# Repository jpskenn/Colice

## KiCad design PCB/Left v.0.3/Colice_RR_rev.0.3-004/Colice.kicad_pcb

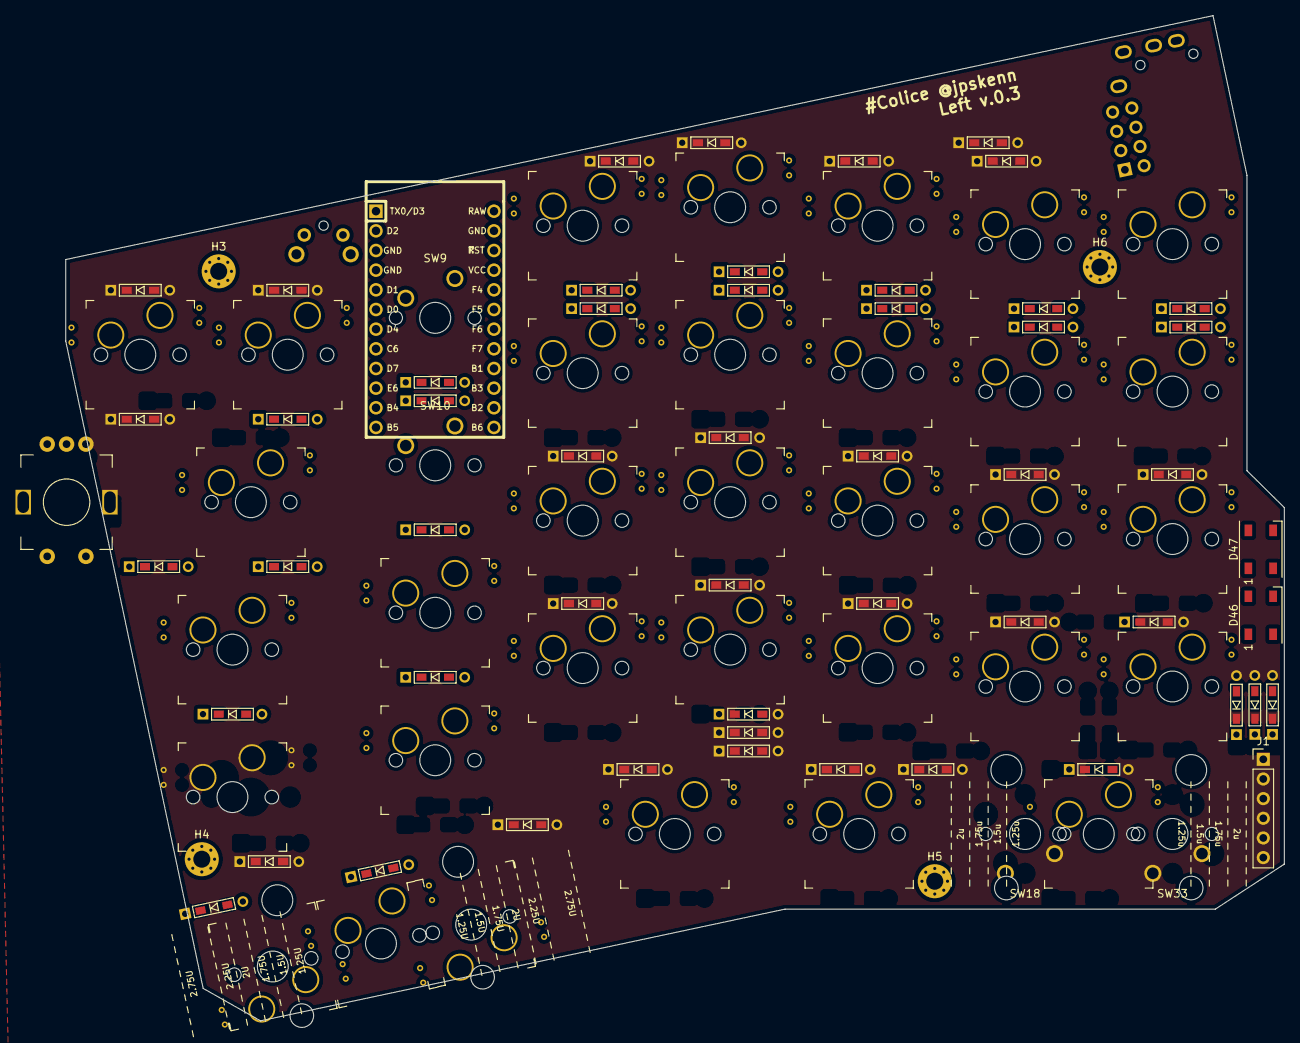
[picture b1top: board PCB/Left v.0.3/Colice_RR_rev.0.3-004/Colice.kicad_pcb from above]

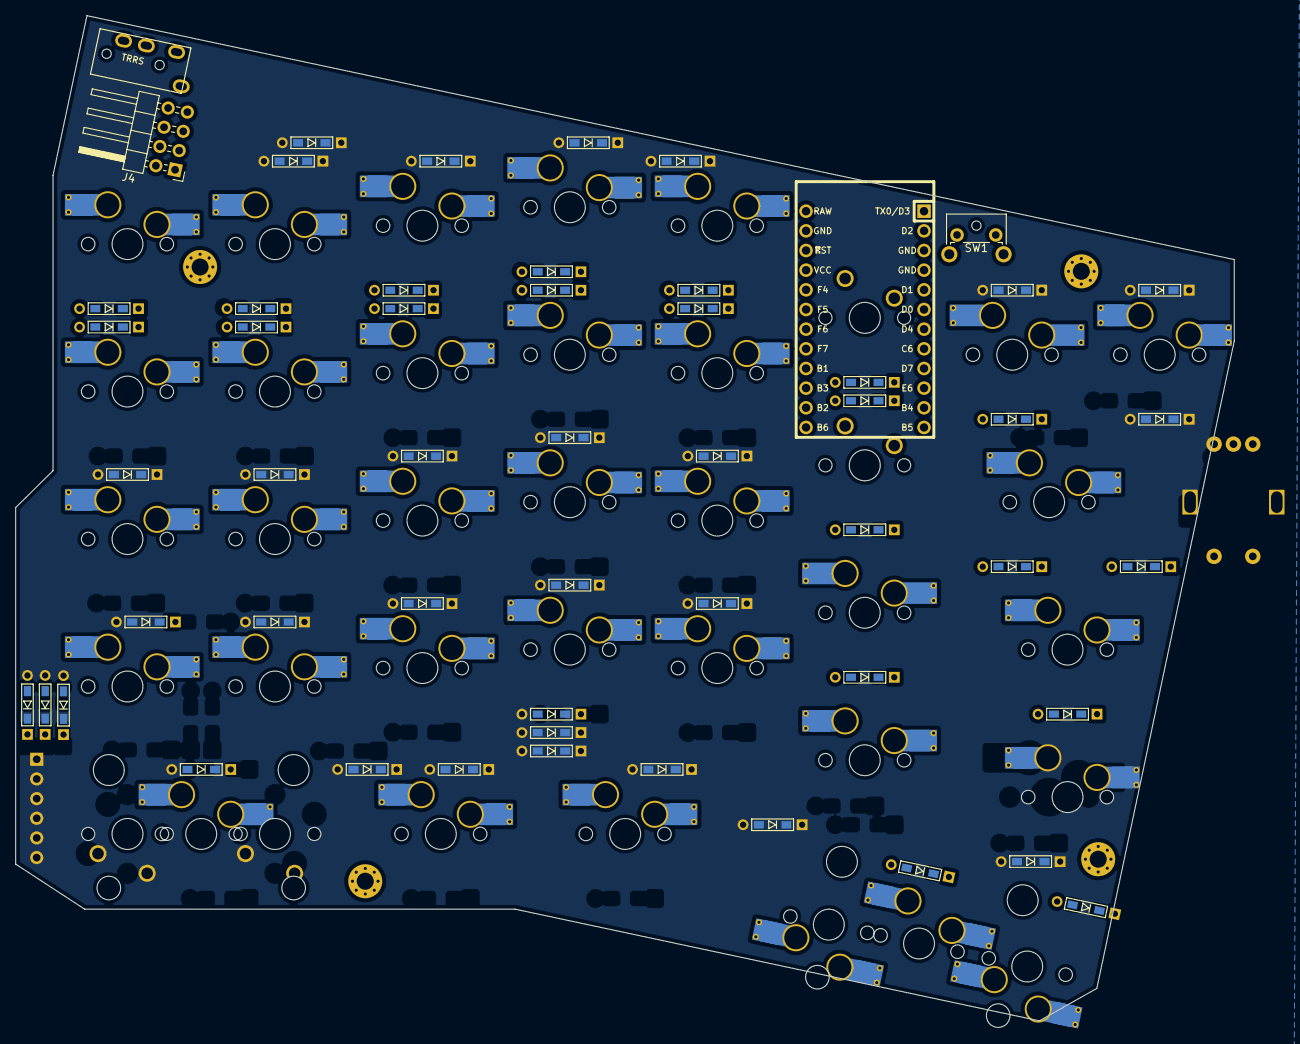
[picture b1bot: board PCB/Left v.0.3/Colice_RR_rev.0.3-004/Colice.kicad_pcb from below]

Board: 2 copper layers, 157.4 x 129.9 mm, 101 parts (4 on the bottom side), 68 nets, no tracks yet.

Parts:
D1, D2, D3, D4, D5, D6, D7, D8, D9, D10, D11, D12, D13, D14, D15, D16, D17, D18, D19, D20, D21, D22, D23, D24, D25, D26, D27, D28, D29, D30, D31, D32, D33, D34, D35, D36, D37, D38, D39, D40, D41, D42, D43, D44, D45, D48, D49, D50, D51, D52: D; D3_TH_SMD
D46, D47: WS2812B; LED_WS2812B_PLCC4_5.0x5.0mm_P3.2mm
H1: MountingHole; CherryMX_MidHeight_Choc_Hotswap_2U_Outline
H2: MountingHole; CherryMX_MidHeight_Choc_Hotswap_2.75U_Outline
H3, H4, H5, H6: MountingHole; MountingHole_2.2mm_M2_Pad_Via
J1: Conn_01x06; PinHeader_1x06_P2.54mm_Vertical
J3: MJ-4PP-9
J4: Conn_02x04_Counter_Clockwise; PinHeader_2x04_P2.54mm_Horizontal
SW1: SW_Push; SW_Tactile_SPST_Angled_MJTP1117
SW2, SW3, SW4, SW5, SW6, SW7, SW8, SW11, SW12, SW13, SW14, SW15, SW16, SW17, SW19, SW20, SW21, SW22, SW23, SW24, SW25, SW26, SW27, SW28, SW29, SW30, SW31, SW32, SW34, SW35, SW36, SW37, SW38: SW_Push; CherryMX_Hotswap_v2
SW9, SW10, SW18, SW33: SW_Push; SW_Cherry_MX1A_1.00u_PCB
SW39: Rotary_Encoder_Switch; RotaryEncoder_Alps_EC11E-Switch_Vertical_H20mm_rev2
U1: ProMicro; ArduinoProMicro

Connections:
GND1: D46.3, D47.3, J3.C, SW1.2, SW39.C, U1.3, U1.4, U1.23
unnamed: D2.2, SW2.2
unnamed: D3.2, SW3.2
unnamed: D4.1, SW4.1, SW5.1, SW6.1, SW7.1, SW8.1, SW13.1
unnamed: D5.2, SW4.2
unnamed: D6.2, SW5.2
unnamed: D7.2, SW6.2
unnamed: D8.2, SW7.2
unnamed: D9.2, SW8.2, SW13.2
unnamed: D10.1, SW9.1, SW10.1, SW11.1, SW12.1
unnamed: D11.2, SW9.2
unnamed: D12.2, SW10.2
unnamed: D13.2, SW11.2
unnamed: D14.2, SW12.2
unnamed: D16.1, SW14.1, SW15.1, SW16.1, SW17.1
unnamed: D17.2, SW14.2
unnamed: D18.2, SW15.2
unnamed: D19.2, SW16.2
unnamed: D20.2, SW17.2
unnamed: D21.2, SW18.2
unnamed: D22.1, SW19.1, SW20.1, SW21.1, SW22.1, SW23.1
unnamed: D23.2, SW19.2
unnamed: D24.2, SW20.2
unnamed: D25.2, SW21.2
unnamed: D26.2, SW22.2
unnamed: D27.2, SW23.2
unnamed: D28.1, SW24.1, SW25.1, SW26.1, SW27.1, SW28.1
unnamed: D29.2, SW24.2
unnamed: D30.2, SW25.2
unnamed: D31.2, SW26.2
unnamed: D32.2, SW27.2
unnamed: D33.2, SW28.2
unnamed: D34.1, SW29.1, SW30.1, SW31.1, SW32.1, SW33.1, SW38.1
unnamed: D35.2, SW29.2
unnamed: D36.2, SW30.2
unnamed: D37.2, SW31.2
unnamed: D38.2, SW32.2
unnamed: D39.1, J1.6
unnamed: D40.1, SW18.1, SW34.1, SW35.1, SW36.1, SW37.1
unnamed: D41.2, SW34.2
unnamed: D42.2, SW35.2
unnamed: D43.2, SW36.2
unnamed: D44.2, SW37.2
unnamed: D45.2, SW33.2, SW38.2
unnamed: D46.2, D47.4
unnamed: D48.2, J1.4
unnamed: D49.2, J1.5
unnamed: D50.2, J1.1
unnamed: D51.2, J1.2
unnamed: D52.2, J1.3
VCC: D46.1, D47.1, J3.D, U1.21
data: J3.B, U1.2
encA: SW39.A, U1.20
encB: SW39.B, U1.19
encS1: D1.1, SW2.1, SW3.1, SW39.S1
encS2: D15.2, SW39.S2
led: D46.4, U1.1
pin1: D2.1, D5.1, D11.1, D16.2, D50.1, U1.17
pin2: D6.1, D12.1, D15.1, D22.2, D51.1, U1.16
pin3: D7.1, D13.1, D28.2, D52.1, U1.15
pin4: D8.1, D14.1, D34.2, D48.1, U1.14
pin5: D3.1, D9.1, D40.2, D49.1, U1.13
pin6: D17.1, D23.1, D29.1, D35.1, D39.2, D41.1, J4.1, U1.8
pin7: D18.1, D24.1, D30.1, D36.1, D42.1, J4.2, U1.9
pin8: D1.2, D19.1, D25.1, D31.1, D37.1, D43.1, J4.3, U1.10
pin9: D4.2, D20.1, D26.1, D32.1, D38.1, D44.1, J4.4, U1.11
pin10: D10.2, D21.1, D27.1, D33.1, D45.1, J4.5, U1.12
reset: SW1.1, U1.22

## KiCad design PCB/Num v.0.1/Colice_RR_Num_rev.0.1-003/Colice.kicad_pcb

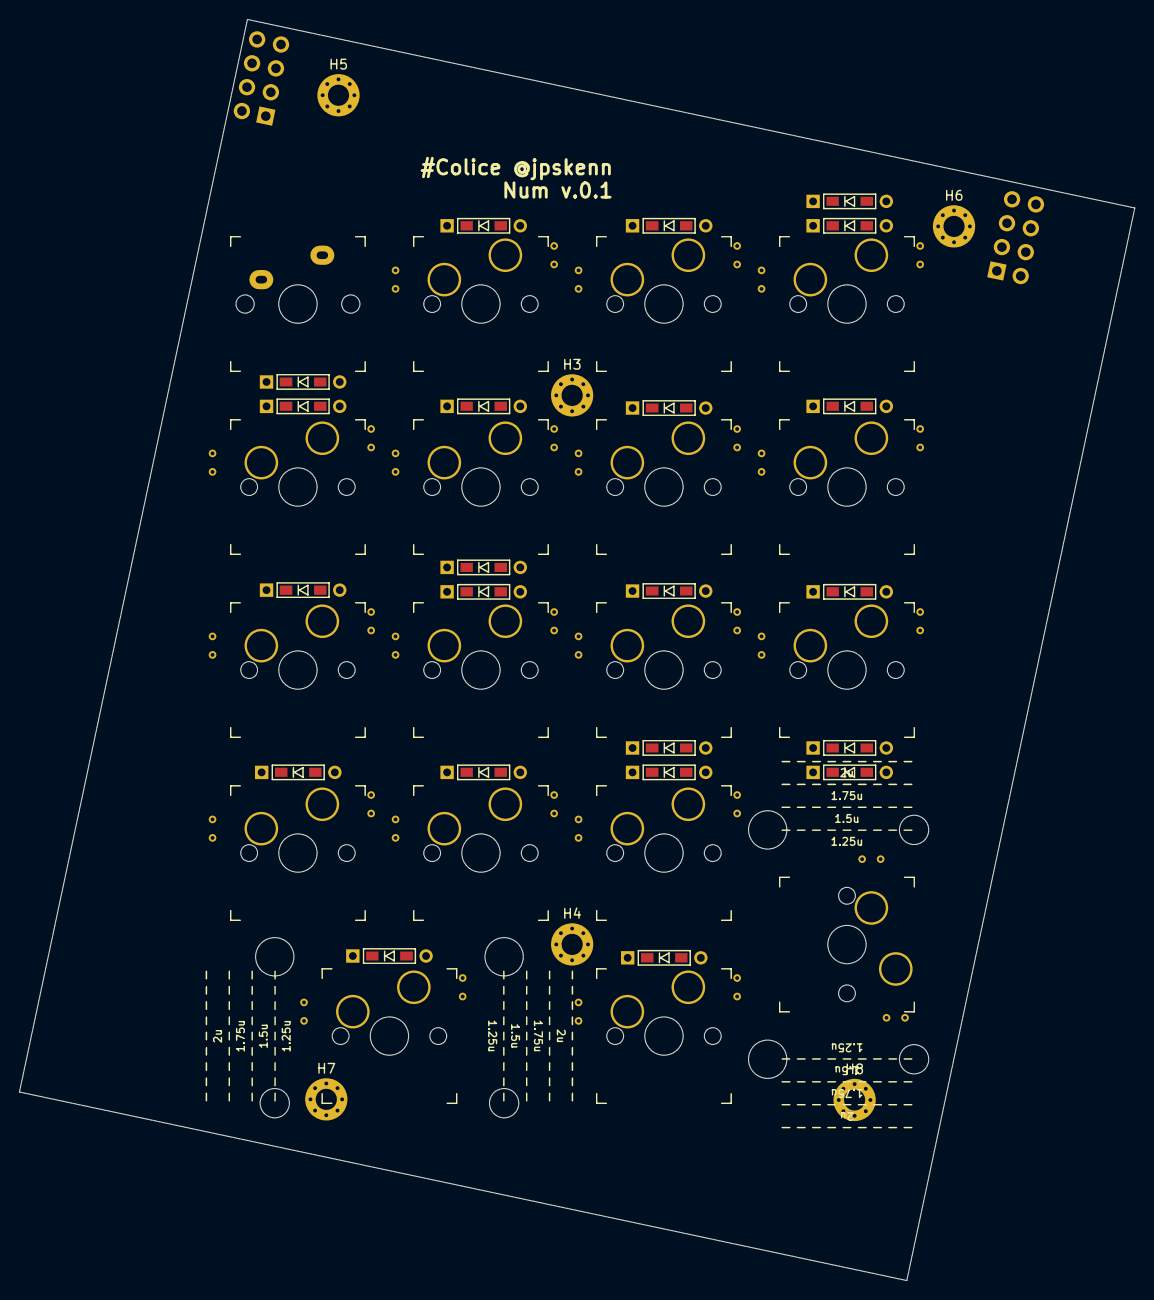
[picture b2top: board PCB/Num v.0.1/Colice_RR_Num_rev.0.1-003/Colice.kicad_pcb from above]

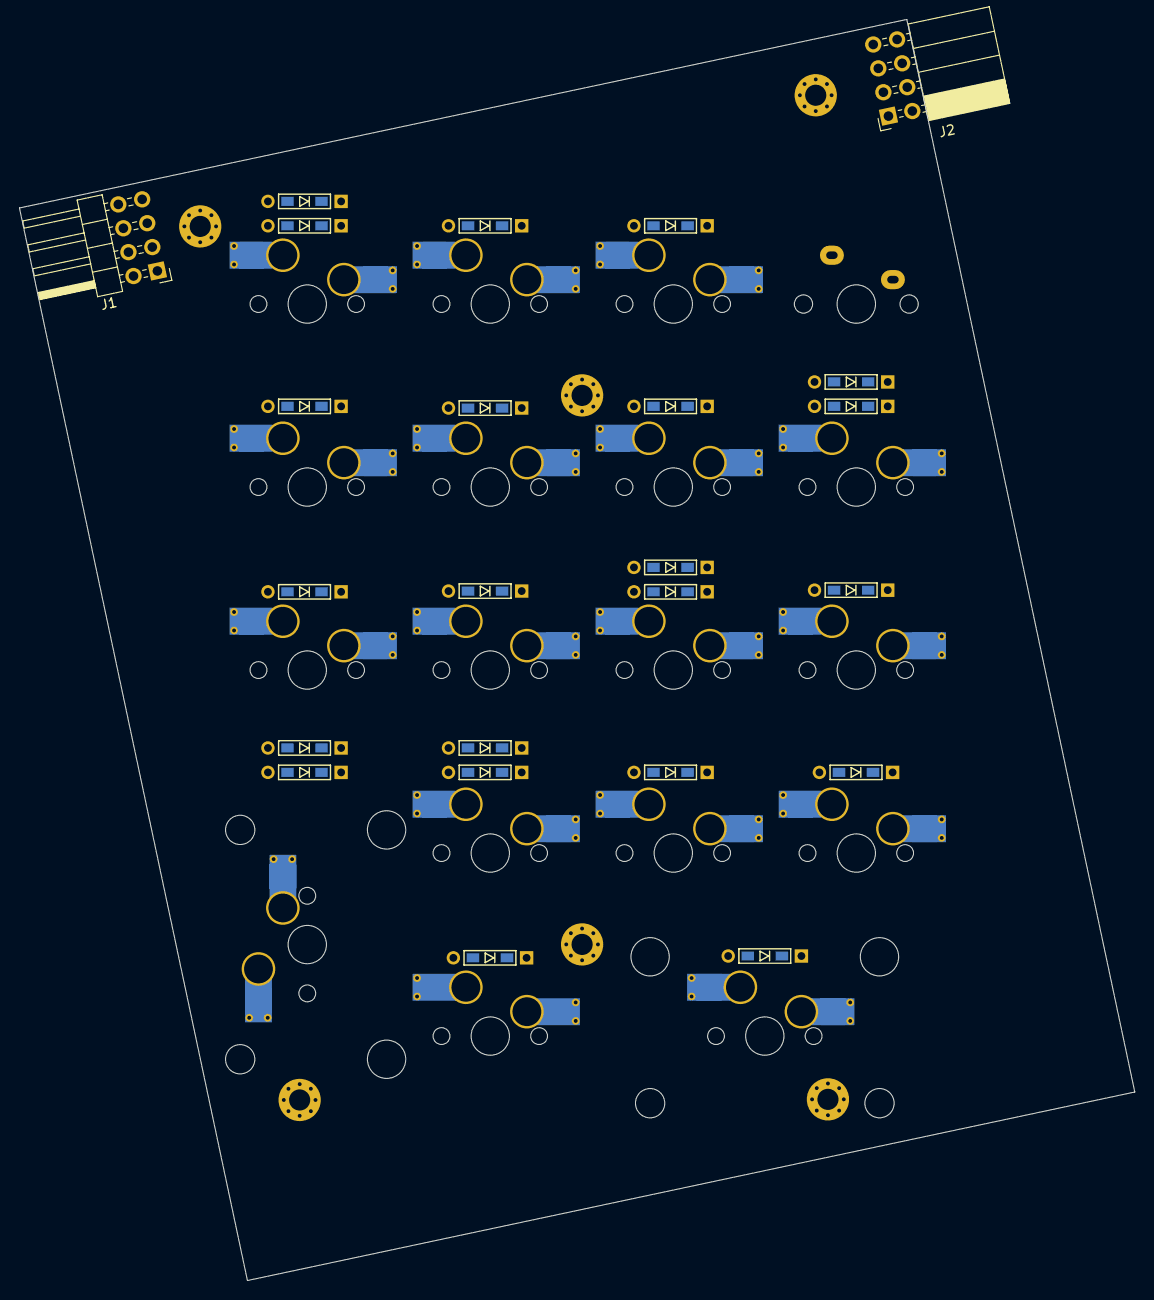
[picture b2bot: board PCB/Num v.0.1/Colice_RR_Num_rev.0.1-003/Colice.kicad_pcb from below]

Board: 2 copper layers, 116.1 x 131.3 mm, 50 parts (2 on the bottom side), 30 nets, no tracks yet.

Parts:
D1, D2, D3, D4, D5, D6, D7, D8, D9, D10, D11, D12, D13, D14, D15, D16, D17, D18, D19, D20, D21, D22: D; D3_TH_SMD
H1, H2: MountingHole; CherryMX_MidHeight_Choc_Hotswap_2U_Outline
H3, H4, H5, H6, H7, H8: MountingHole; MountingHole_2.2mm_M2_Pad_Via
J1: Conn_02x04_Counter_Clockwise; PinHeader_2x04_P2.54mm_Horizontal
J2: Conn_02x04_Counter_Clockwise; PinSocket_2x04_P2.54mm_Horizontal
SW1: SW_PUSH; CherryMX_1u
SW1#2, SW2, SW3, SW4, SW5, SW6, SW7, SW8, SW9, SW10, SW11, SW12, SW13, SW14, SW15, SW16, SW17: SW_Push; CherryMX_Hotswap_v2

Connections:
GND: J1.7, J2.7
unnamed: D1.2, SW1#2.2
unnamed: D2.2, SW2.2
unnamed: D3.2, SW3.2
unnamed: D4.2, SW4.2
unnamed: D5.2, SW5.2
unnamed: D6.2, SW6.2
unnamed: D7.2, SW7.2
unnamed: D8.2, SW8.2
unnamed: D9.2, SW9.2
unnamed: D10.2, SW10.2
unnamed: D11.2, SW11.2
unnamed: D12.2, SW12.2
unnamed: D13.2, SW13.2
unnamed: D14.2, SW14.2
unnamed: D15.2, SW15.2
unnamed: D16.2, SW16.2
unnamed: D17.2, SW17.2
unnamed: D18.1, SW14.1, SW15.1, SW16.1
unnamed: D19.1, SW1#2.1, SW2.1, SW3.1, SW4.1
unnamed: D20.1, SW7.1, SW8.1
unnamed: D21.1, SW5.1, SW6.1, SW12.1, SW13.1
unnamed: D22.1, SW9.1, SW10.1, SW11.1, SW17.1
VCC: J1.8, J2.8
data: J1.6, J2.6
pin6: D5.1, D9.1, D14.1, D19.2, J2.1
pin7: D1.1, D6.1, D10.1, D15.1, D20.2, J2.2
pin8: D2.1, D7.1, D11.1, D16.1, D21.2, J2.3
pin9: D3.1, D8.1, D12.1, D22.2, J2.4
pin10: D4.1, D13.1, D17.1, D18.2, J2.5

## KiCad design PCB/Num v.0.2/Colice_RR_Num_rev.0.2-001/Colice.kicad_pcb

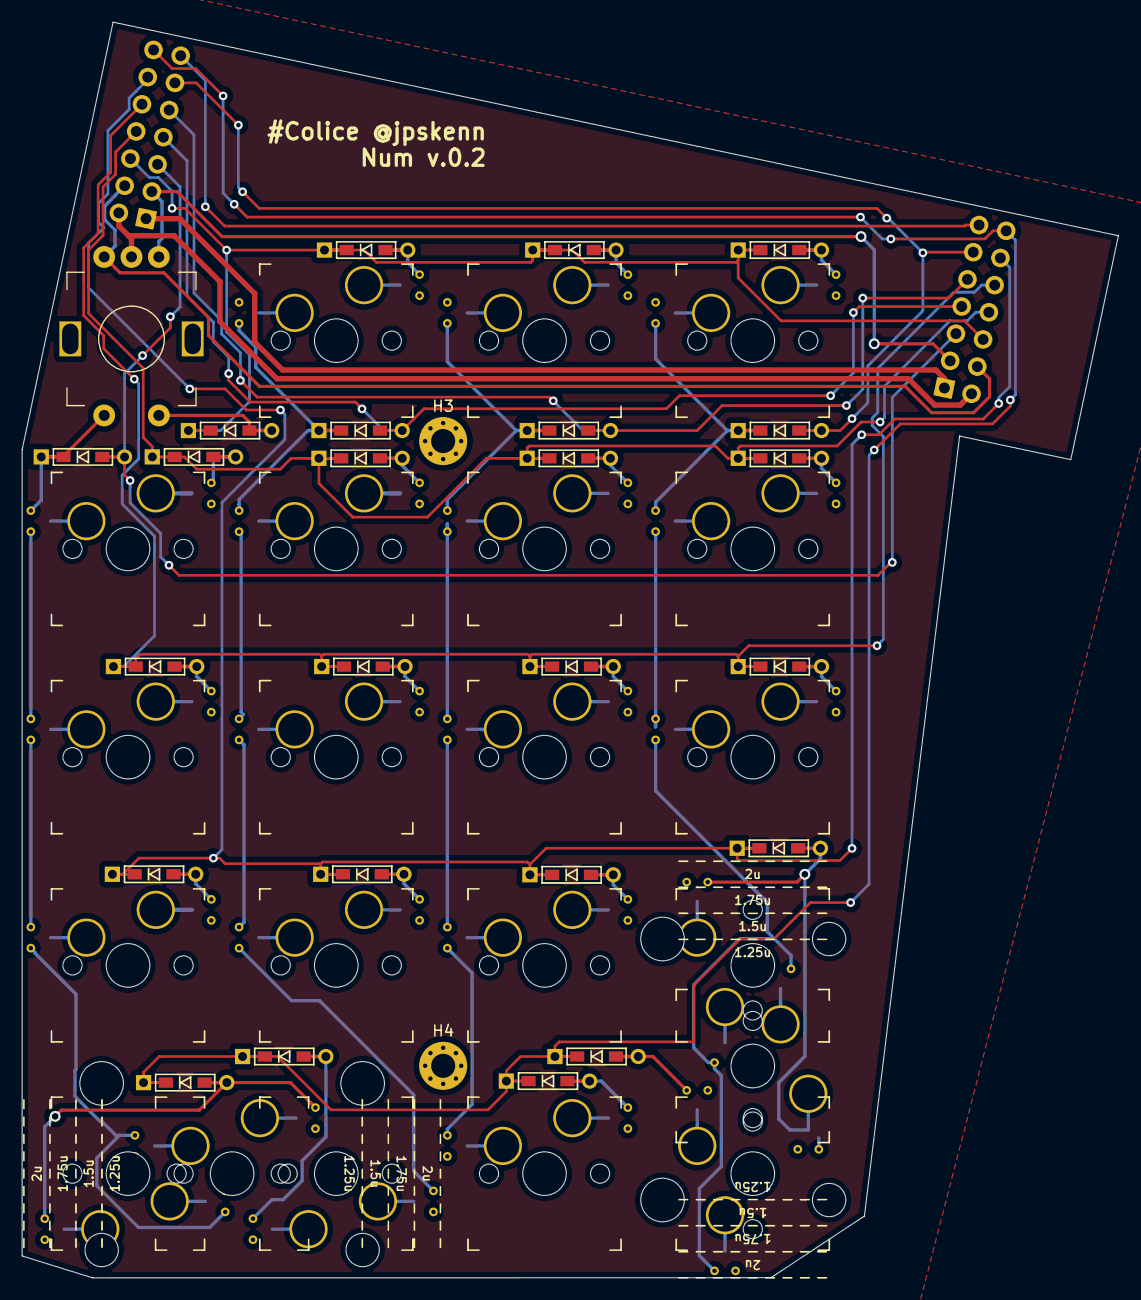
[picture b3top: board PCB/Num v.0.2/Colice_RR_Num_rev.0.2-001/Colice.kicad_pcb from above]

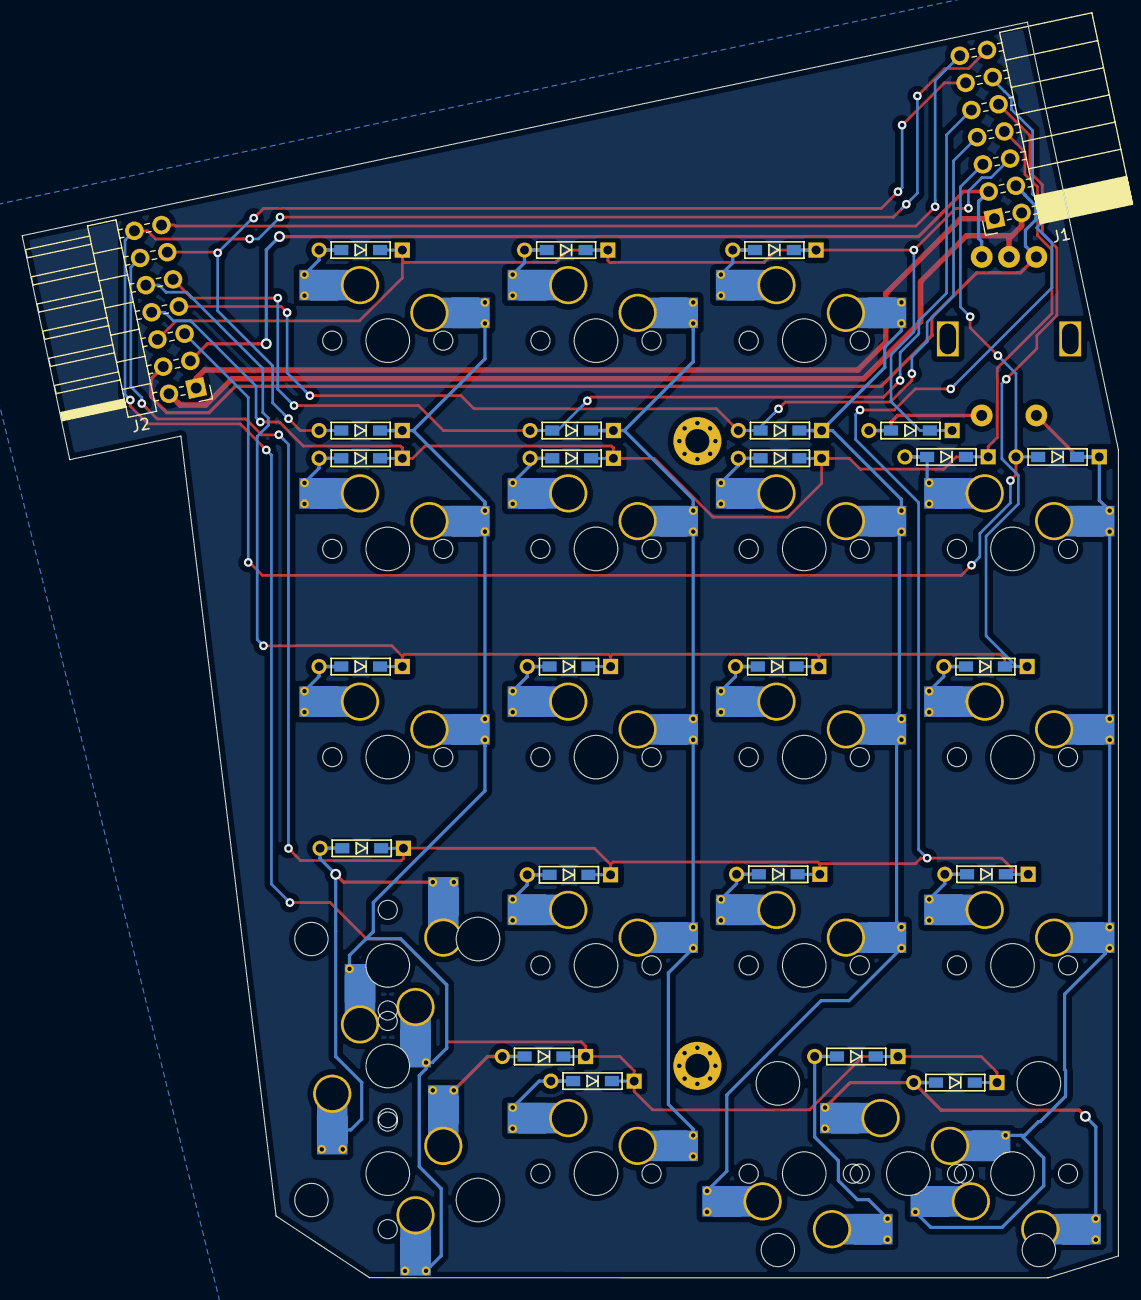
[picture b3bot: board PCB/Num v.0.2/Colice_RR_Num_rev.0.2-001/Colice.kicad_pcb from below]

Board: 2 copper layers, 100.3 x 114.9 mm, 52 parts (2 on the bottom side), 38 nets.

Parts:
D1, D2, D3, D4, D5, D6, D7, D8, D9, D10, D11, D12, D13, D14, D15, D16, D17, D18, D19, D20, D21, D22, D23, D24: D; D3_TH_SMD
H1, H2: MountingHole; CherryMX_MidHeight_Choc_Hotswap_2U_Outline
H3, H4: MountingHole; MountingHole_2.2mm_M2_Pad_Via
J1: Conn_02x07_Odd_Even; PinSocket_2x07_P2.54mm_Horizontal
J2: Conn_02x07_Odd_Even; PinHeader_2x07_P2.54mm_Horizontal
SW1, SW2, SW3, SW4, SW5, SW6, SW7, SW8, SW9, SW10, SW11, SW12, SW13, SW14, SW15, SW16, SW17, SW18, SW19, SW20, SW21: SW_Push; CherryMX_Hotswap_v2
SW22: Rotary_Encoder_Switch; RotaryEncoder_Alps_EC11E-Switch_Vertical_H20mm_rev2

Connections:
GND_source: J1.2, J2.2, SW22.C
unnamed: D2.2, SW1.2
unnamed: D3.2, SW2.2
unnamed: D4.2, SW3.2
unnamed: D5.2, SW4.2, SW20.2
unnamed: D6.1, SW5.1, SW6.1, SW7.1, SW8.1, SW18.1
unnamed: D7.2, SW5.2
unnamed: D8.2, SW6.2
unnamed: D9.2, SW7.2
unnamed: D10.2, SW8.2
unnamed: D11.1, SW9.1, SW10.1, SW11.1, SW12.1, SW13.1
unnamed: D12.2, SW9.2
unnamed: D13.2, SW10.2
unnamed: D14.2, SW11.2
unnamed: D15.2, SW12.2
unnamed: D16.2, SW13.2
unnamed: D17.1, SW14.1, SW15.1, SW16.1, SW17.1, SW19.1, SW21.1
unnamed: D18.2, SW14.2
unnamed: D19.2, SW15.2
unnamed: D20.2, SW16.2
unnamed: D21.2, SW17.2, SW21.2
unnamed: D22.2, SW18.2
unnamed: D23.2, SW19.2
VCC_source: J1.1, J2.1
data-encA: J1.3, J2.3, SW22.A
encS1: D1.1, SW1.1, SW2.1, SW3.1, SW4.1, SW20.1, SW22.S1
encS2: D24.2, SW22.S2
extra-encB: J1.4, J2.4, SW22.B
pin1: D1.2, J1.5, J2.5
pin2: D6.2, J1.7, J2.7
pin3: D11.2, J1.9, J2.9
pin4: D17.2, J1.11, J2.11
pin5: J1.13, J2.13
pin6: D7.1, D12.1, D18.1, D24.1, J1.6, J2.6
pin7: D2.1, D8.1, D13.1, D19.1, J1.8, J2.8
pin8: D3.1, D9.1, D14.1, D20.1, J1.10, J2.10
pin9: D4.1, D10.1, D15.1, D21.1, J1.12, J2.12
pin10: D5.1, D16.1, D22.1, D23.1, J1.14, J2.14
